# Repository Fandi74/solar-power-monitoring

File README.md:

***Solar Monitoring System***

This repository contains the source code for a Solar Monitoring System using ESP32 for data acquisition, storage, and logging. The system reads data from solar panels, calculates power values, and logs the information locally or sends it to the cloud.

**Features**
- Real-time monitoring of voltage, current, and power from two solar panels.
- Data logging to an SD card in JSON format.
- Time synchronization with NTP servers.
- LCD display for live data visualization.
- Modular design with FreeRTOS tasks.

**Project Structure**
- main.cpp: ESP32-based code for the actual deployment.
- hardware/: Contains schematics, footprints PCBs, Simulation.

**Software Dependencies**

- PlatformIO (for development).
- Libraries:
  - Adafruit_ADS1X15
  - ArduinoJson
  - LiquidCrystal_I2C
  - WiFi
  - HTTPClient
  - RTC3231
- Proteus for simulation (using Arduino Uno).

**Future Enhancements**
- Implement cloud integration for remote monitoring.
- Add additional panels and sensors for scalability.
- Enhance data visualization with a web dashboard.

****I Made all of this just for fun****
Feel free give any feedback

**3D PCB**

**Schematic**

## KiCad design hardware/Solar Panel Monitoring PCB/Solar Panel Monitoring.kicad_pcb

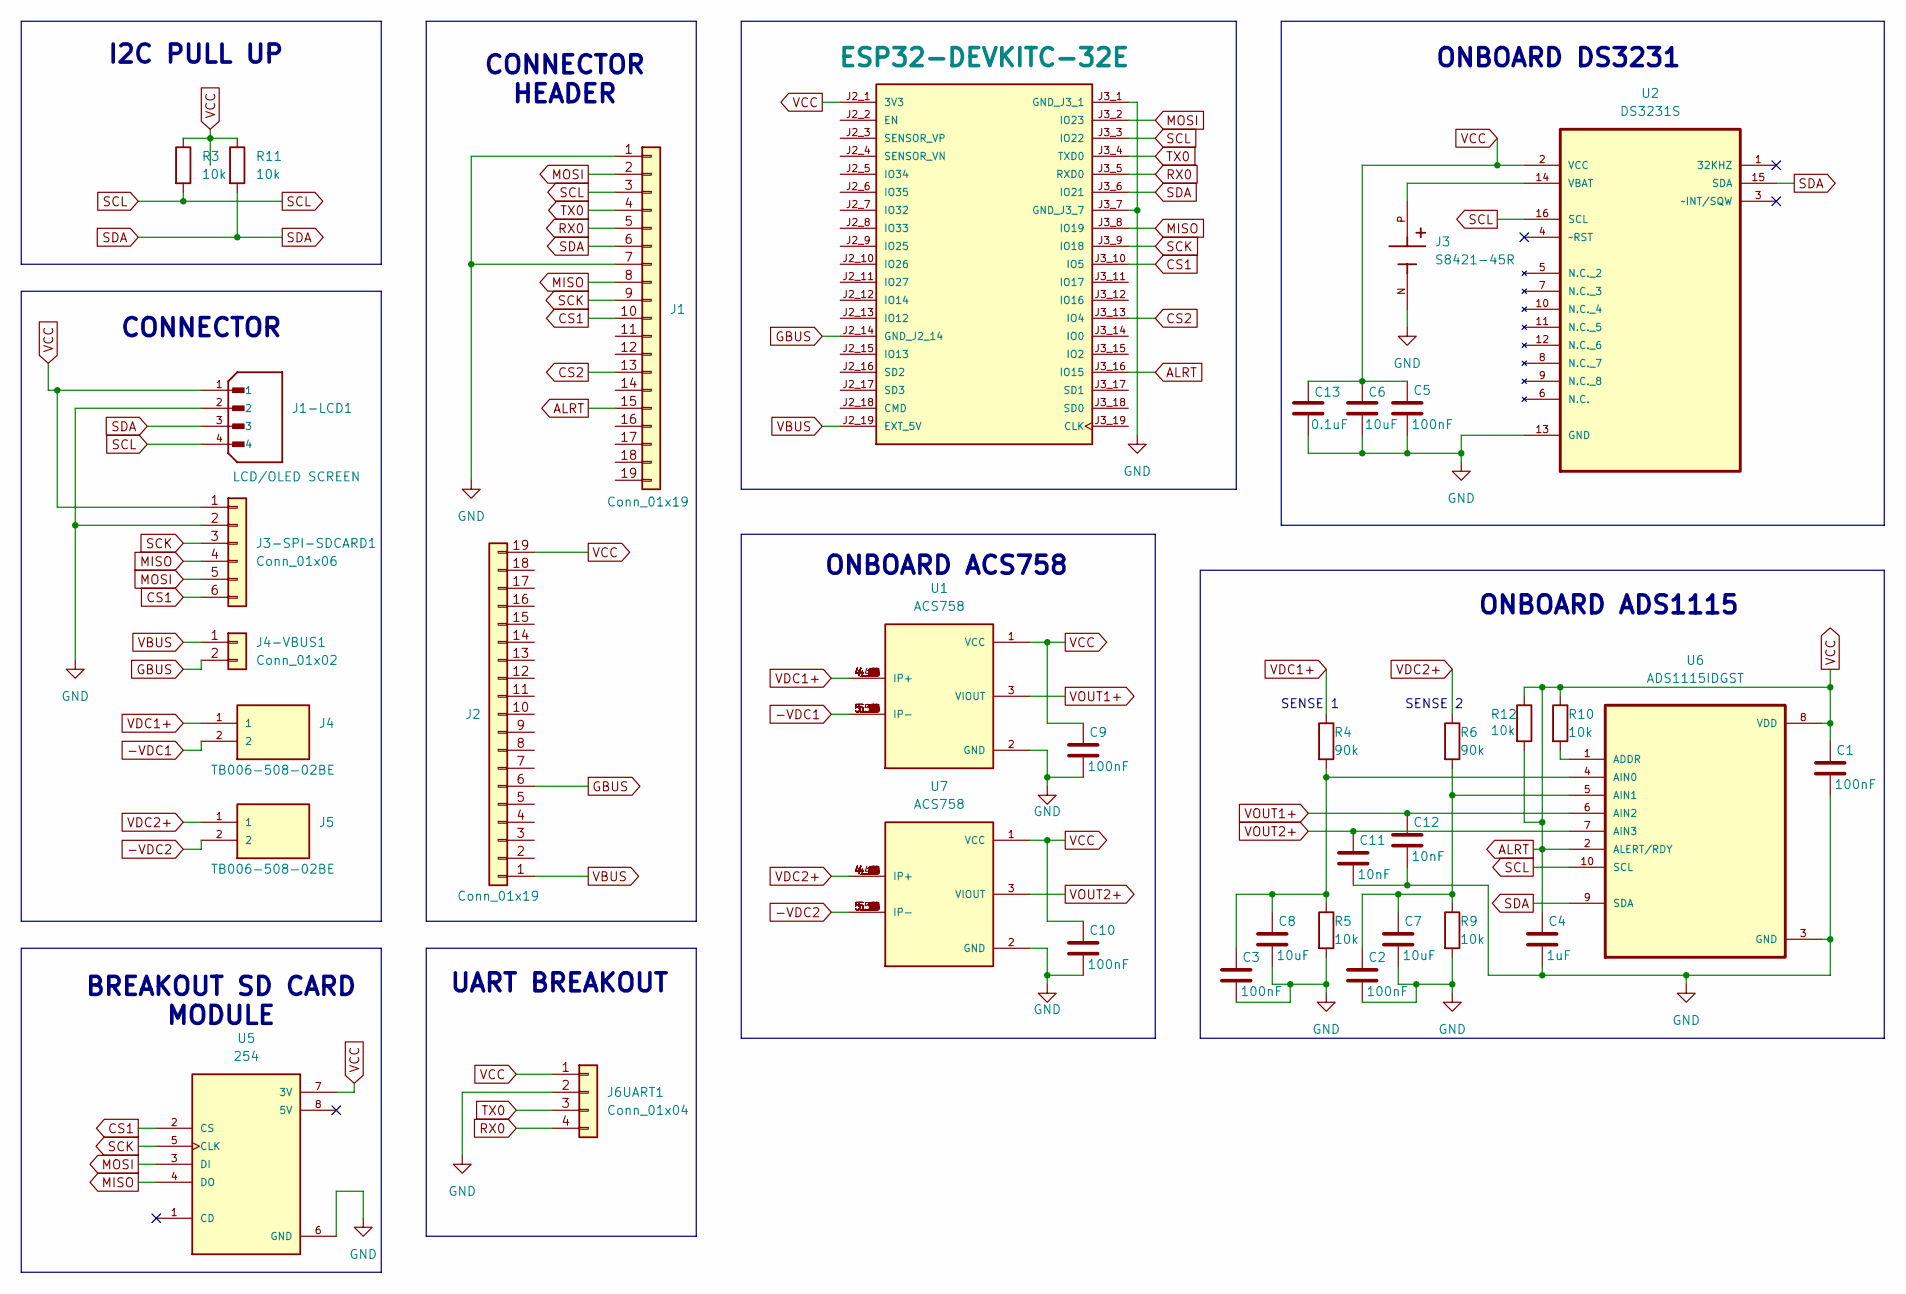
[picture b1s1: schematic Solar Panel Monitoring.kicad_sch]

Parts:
C1, C2, C3, C5, C9, C10: 100nF; C_0603_1608Metric
C4: 1uF; C_0603_1608Metric
C6, C7, C8: 10uF; C_0603_1608Metric
C11, C12: 10nF; C_0603_1608Metric
C13: 0.1uF; C_0603_1608Metric
J1, J2: Conn_01x19; PinSocket_1x19_P2.54mm_Vertical
J1-LCD1: LCD/OLED SCREEN; JST_B4B-XH-A_LF__SN_; PARTREV 7/4/21
J3: S8421-45R; HARWIN_S8421-45R; PARTREV 7
J3-SPI-SDCARD1: Conn_01x06; PinHeader_1x06_P2.54mm_Vertical
J4, J5: TB006-508-02BE; CUI_TB006-508-02BE
J4-VBUS1: Conn_01x02; JST_EH_B02B-EH-A_02x2.50mm_Straight
J6UART1: Conn_01x04; PinHeader_1x04_P2.54mm_Vertical
R3, R10, R11, R12: 10k; R_0805_2012Metric_Pad1.20x1.40mm_HandSolder
R4, R6: 90k; R_1210_3225Metric_Pad1.30x2.65mm_HandSolder
R5, R9: 10k; R_1210_3225Metric_Pad1.30x2.65mm_HandSolder
U1, U7: ACS758; XDCR_ACS758; PARTREV 12
U2: DS3231S; SOIC127P1032X265-16N; MPN DS3231S#
U4: ESP32-DEVKITC-32E; MODULE_ESP32-DEVKITC-32E; PARTREV 1.4
U5: 254; MODULE_254; PARTREV Jul 31, 2013
U6: ADS1115IDGST; SOP50P490X110-10N

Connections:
-VDC1: J4.2, U1.5 (IP-), U1.5_1 (IP-), U1.5_2 (IP-), U1.5_3 (IP-), U1.5_4 (IP-), U1.5_5 (IP-), U1.5_6 (IP-), U1.5_7 (IP-), U1.5_8 (IP-), U1.5_9 (IP-), U1.5_10 (IP-), U1.5_11 (IP-), U1.5_12 (IP-), U1.5_13 (IP-), U1.5_14 (IP-), U1.5_15 (IP-), U1.5_16 (IP-)
-VDC2: J5.2, U7.5 (IP-), U7.5_1 (IP-), U7.5_2 (IP-), U7.5_3 (IP-), U7.5_4 (IP-), U7.5_5 (IP-), U7.5_6 (IP-), U7.5_7 (IP-), U7.5_8 (IP-), U7.5_9 (IP-), U7.5_10 (IP-), U7.5_11 (IP-), U7.5_12 (IP-), U7.5_13 (IP-), U7.5_14 (IP-), U7.5_15 (IP-), U7.5_16 (IP-)
ALRT: C1.2, C4.2, C5.2, C6.2, C9.2, C10.2, C13.2, J1.15, J1-LCD1.1, J2.19, J3-SPI-SDCARD1.1, J6UART1.1, R3.1, R10.1, R11.1, R12.1, R12.2, U1.1 (VCC), U2.2 (VCC), U4.J2_1 (3V3), U4.J3_16 (IO15), U5.7 (3V), U6.2 (ALERT/RDY), U6.8 (VDD), U7.1 (VCC); also elsewhere on the board
CS1: J1.10, J3-SPI-SDCARD1.6, U4.J3_10 (IO5), U5.2 (CS)
CS2: J1.13, U4.J3_13 (IO4)
GBUS: J2.6, J4-VBUS1.2, U4.J2_14 (GND_J2_14)
GND: C1.1, C2.1, C3.1, C4.1, C5.1, C6.1, C7.1, C8.1, C9.1, C10.1, C11.1, C12.1, C13.1, J1.1, J1.7, J1-LCD1.2, J3.N, J3-SPI-SDCARD1.2, J6UART1.2, R5.2, R9.2, U1.2 (GND), U2.13 (GND), U4.J3_1 (GND_J3_1), U4.J3_7 (GND_J3_7), U5.6 (GND), U6.3 (GND), U7.2 (GND); also elsewhere on the board
MISO: J1.8, J3-SPI-SDCARD1.4, U4.J3_8 (IO19), U5.4 (DO)
MOSI: J1.2, J3-SPI-SDCARD1.5, U4.J3_2 (IO23), U5.3 (DI)
unnamed: J3.P, U2.14 (VBAT)
unnamed: R10.2, U6.1 (ADDR)
unnamed: C3.2, C8.2, R4.2, R5.1, U6.4 (AIN0)
unnamed: C2.2, C7.2, R6.2, R9.1, U6.5 (AIN1)
RX0: J1.5, J6UART1.4, U4.J3_5 (RXD0); also elsewhere on the board
SCK: J1.9, J3-SPI-SDCARD1.3, U4.J3_9 (IO18), U5.5 (CLK)
SCL: J1.3, J1-LCD1.4, R3.2, U2.16 (SCL), U4.J3_3 (IO22), U6.10 (SCL)
SDA: J1.6, J1-LCD1.3, R11.2, U2.15 (SDA), U4.J3_6 (IO21), U6.9 (SDA)
TX0: J1.4, J6UART1.3, U4.J3_4 (TXD0); also elsewhere on the board
VBUS: J2.1, J4-VBUS1.1, U4.J2_19 (EXT_5V)
VDC1+: J4.1, R4.1, U1.4 (IP+), U1.4_1 (IP+), U1.4_2 (IP+), U1.4_3 (IP+), U1.4_4 (IP+), U1.4_5 (IP+), U1.4_6 (IP+), U1.4_7 (IP+), U1.4_8 (IP+), U1.4_9 (IP+), U1.4_10 (IP+), U1.4_11 (IP+), U1.4_12 (IP+), U1.4_13 (IP+), U1.4_14 (IP+), U1.4_15 (IP+), U1.4_16 (IP+)
VDC2+: J5.1, R6.1, U7.4 (IP+), U7.4_1 (IP+), U7.4_2 (IP+), U7.4_3 (IP+), U7.4_4 (IP+), U7.4_5 (IP+), U7.4_6 (IP+), U7.4_7 (IP+), U7.4_8 (IP+), U7.4_9 (IP+), U7.4_10 (IP+), U7.4_11 (IP+), U7.4_12 (IP+), U7.4_13 (IP+), U7.4_14 (IP+), U7.4_15 (IP+), U7.4_16 (IP+)
VOUT1+: C12.2, U1.3 (VIOUT), U6.6 (AIN2)
VOUT2+: C11.2, U6.7 (AIN3), U7.3 (VIOUT)

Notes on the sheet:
SENSE 2
CONNECTOR HEADER
I2C PULL UP
SENSE 1
ONBOARD ADS1115
CONNECTOR
ONBOARD ACS758
BREAKOUT SD CARD MODULE
UART BREAKOUT
ONBOARD DS3231

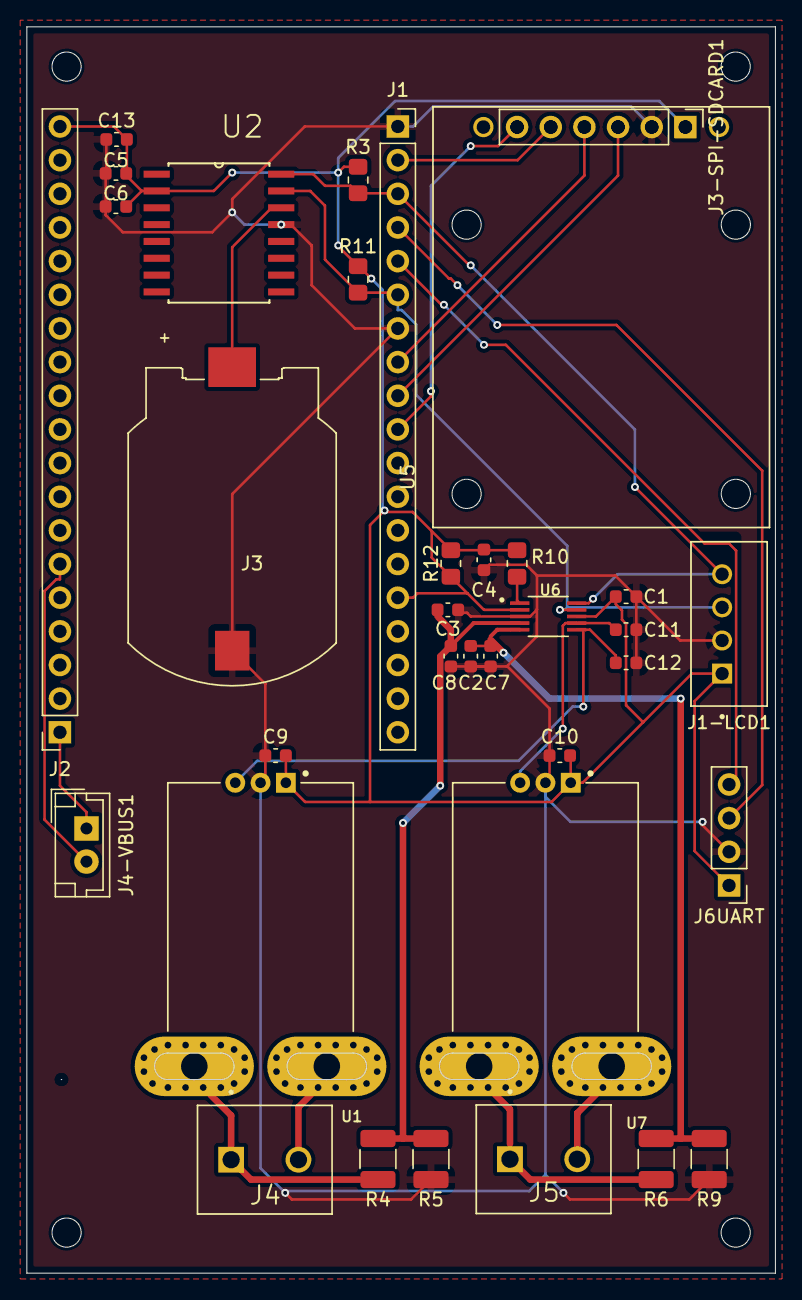
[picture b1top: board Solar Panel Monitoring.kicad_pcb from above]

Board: 2 copper layers, 56.5 x 94.1 mm, 35 parts (0 on the bottom side), 22 nets.

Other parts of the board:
J6UART: Conn_01x04; PinHeader_1x04_P2.54mm_Vertical

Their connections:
ALRT: J6UART.1; also elsewhere on the board
GND: J6UART.2; also elsewhere on the board
RX0: J6UART.4; also elsewhere on the board
TX0: J6UART.3; also elsewhere on the board

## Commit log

2025-01-14 add hardware files
2025-01-15 update hardware
2025-01-23 add asset
